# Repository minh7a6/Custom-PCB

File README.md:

# Custom-PCB
This is where I put my pcb and schematic that I created and used for projects.
PCB is created in Autodesk EAGLE.
For company to make those and get all the , I would recommend JLCPCB and LCSC for those since they are fast and quite cheap
You can use it and do whatever you want to do.
Feel free to put any request or issues. Because I'm still 17 so mistakes is unavoidable.
Enjoy :)

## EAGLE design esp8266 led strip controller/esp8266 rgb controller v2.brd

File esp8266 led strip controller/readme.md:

esp8266 wifi led strip controller

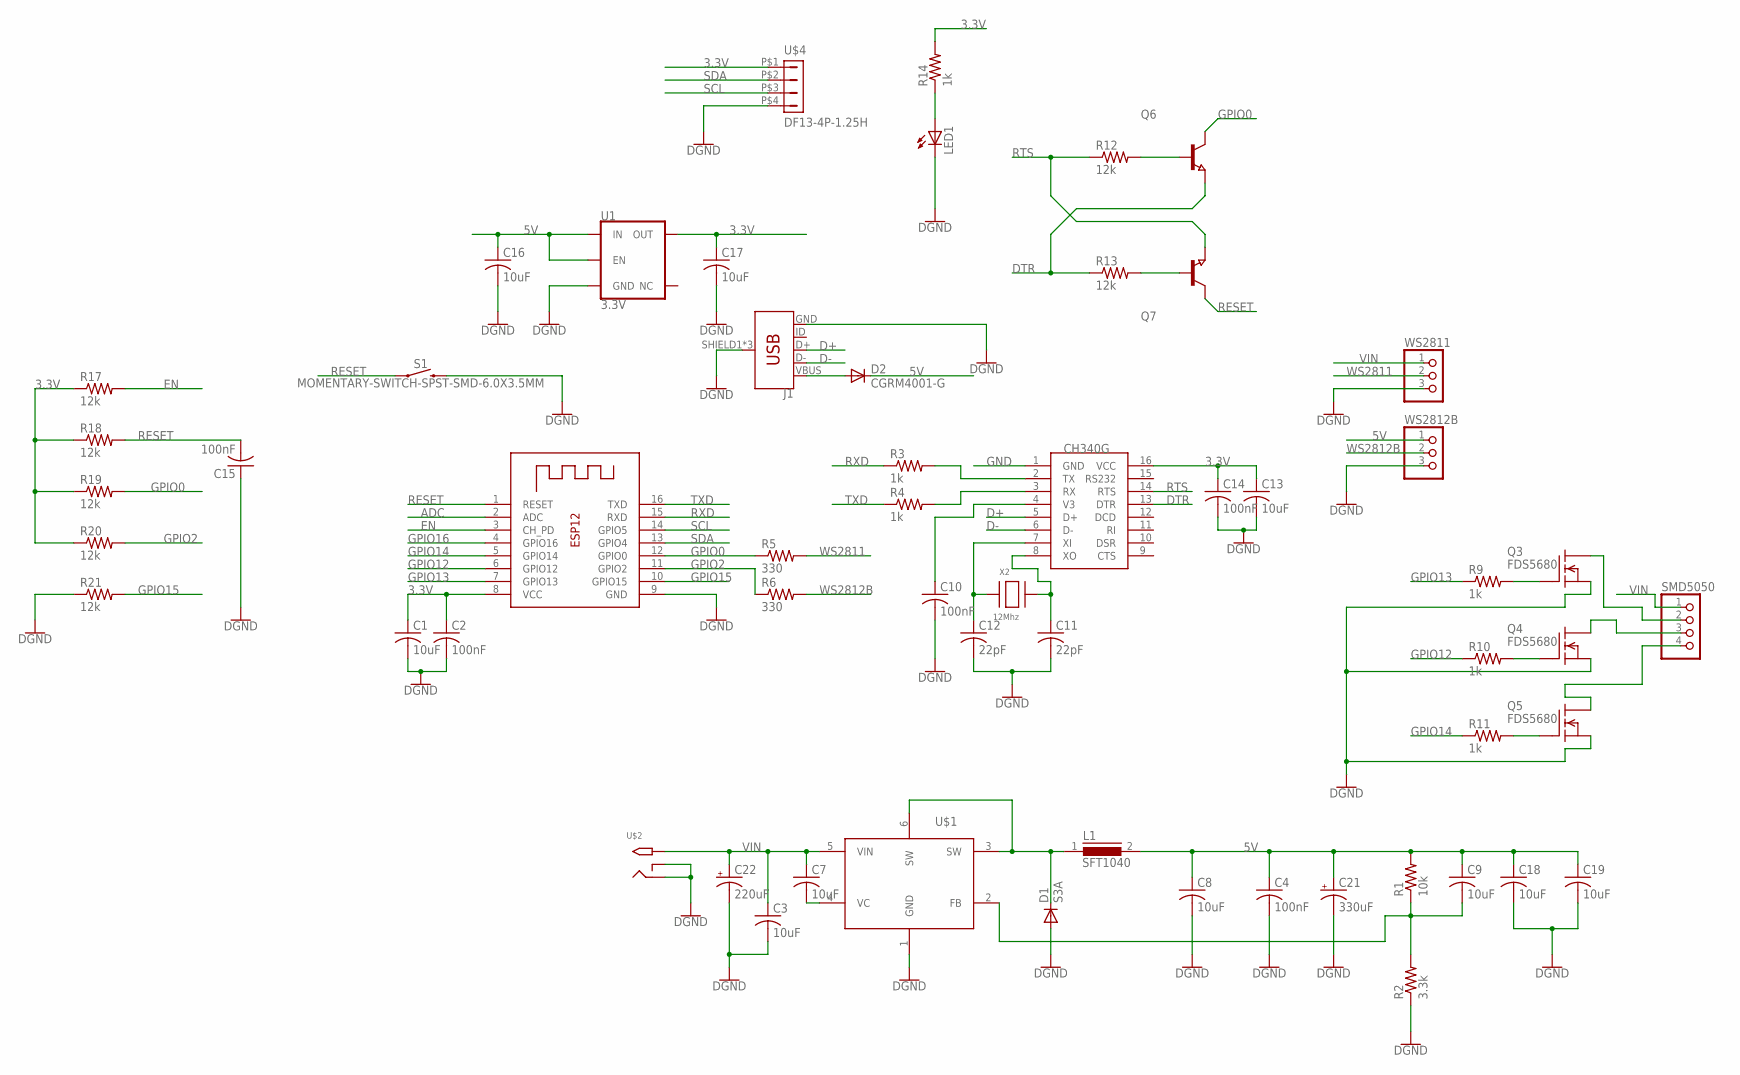
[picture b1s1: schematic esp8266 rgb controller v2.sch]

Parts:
C1, C3, C7, C8, C9, C13, C17, C18, C19: 10uF; C0805
C2, C4, C10, C14, C15: 100nF; C0805
C11, C12: 22pF; C0805
C16: 10uF; C1210
C21: 330uF; 153CLV-0810
C22: 220uF; 153CLV-0810
D1: S3A; DO214AB
D2: CGRM4001-G; SOD-123_MINI-SMA
J1: USB_MICRO-BREDUCED_PASTE; USB-B-MICRO-SMD_RED_PASTE
L1: SFT1040
LED1: LEDCHIP-LED0603; CHIP-LED0603
Q3, Q4, Q5: FDS5680; SO-8
Q6, Q7: NPN-TRANSISTOR_SOT23; SOT23
R1: 10k; R0805
R2: 3.3k; R0805
R3, R4, R9, R10, R11, R14: 1k; R0805
R5, R6: 330; R0805
R12, R13, R17, R18, R19, R20, R21: 12k; R0805
S1: MOMENTARY-SWITCH-SPST-SMD-6.0X3.5MM; TACTILE_SWITCH_SMD_6.0X3.5MM
SMD5050: PINHD-1X4; 1X04
U1: 3.3V; SOT23-5
U$1: XL4015; TO263-5
U$2: 2.1MMJACKTHM; PJ-102A
U$3: CH340G; SOIC16
U$4: DF13-4P-1.25H; DF13A-4P-1.25H
WS2811, WS2812B: PINHD-1X3; 1X03
X1: ESP-12F; ESP-12
X2: 12Mhz; NX5032

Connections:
3.3V: C1.1, C2.1, C13.1, C14.1, C17.1, R14.2, R17.1, R18.1, R19.1, R20.1, U1.5 (OUT), U$3.16 (VCC), U$4.P$1 (1), X1.8 (VCC)
5V: C4.1, C8.1, C9.1, C16.1, C18.1, C19.1, C21.+, D2.C, L1.2, R1.2, U1.1 (IN), U1.3 (EN), WS2812B.1
ADC: X1.2 (ADC)
D+: J1.D+, U$3.5 (D+)
D-: J1.D-, U$3.6 (D-)
DTR: Q6.2 (E), R13.1, U$3.13 (DTR)
EN: R17.2, X1.3 (CH_PD)
GND: C1.2, C2.2, C3.2, C4.2, C8.2, C10.2, C11.2, C12.2, C13.2, C14.2, C15.1, C16.2, C17.2, C18.2, C19.2, C21.-, C22.-, D1.A, J1.GND, J1.SHIELD1 (SHIELD), J1.SHIELD2 (SHIELD), J1.SHIELD3 (SHIELD), LED1.C, Q3.1 (S), Q3.2 (S), Q3.3 (S), Q4.1 (S), Q4.2 (S), Q4.3 (S), Q5.1 (S), Q5.2 (S), Q5.3 (S), R2.1, R21.1, S1.2, U1.2 (GND), U$1.1 (GND), U$2.RING, U$2.RING_SW, U$3.1 (GND), U$4.P$4 (4), WS2811.3, WS2812B.3, X1.9 (GND)
GPIO0: Q6.3 (C), R5.1, R19.2, X1.12 (GPIO0)
GPIO2: R6.1, R20.2, X1.11 (GPIO2)
GPIO12: R10.1, X1.6 (GPIO12)
GPIO13: R9.1, X1.7 (GPIO13)
GPIO14: R11.1, X1.5 (GPIO14)
GPIO15: R21.2, X1.10 (GPIO15)
GPIO16: X1.4 (GPIO16)
unnamed: Q3.5 (D), Q3.6 (D), Q3.7 (D), Q3.8 (D), SMD5050.2
unnamed: D1.C, L1.1, U$1.3 (SW), U$1.6 (SW)
unnamed: Q4.5 (D), Q4.6 (D), Q4.7 (D), Q4.8 (D), SMD5050.3
unnamed: D2.A, J1.VBUS
unnamed: R3.2, U$3.2 (TX)
unnamed: R4.2, U$3.3 (RX)
unnamed: C10.1, U$3.4 (V3)
unnamed: Q5.5 (D), Q5.6 (D), Q5.7 (D), Q5.8 (D), SMD5050.4
unnamed: Q6.1 (B), R12.2
unnamed: C12.1, U$3.7 (XI), X2.P$1
unnamed: C11.1, U$3.8 (XO), X2.P$2
unnamed: Q5.4 (G), R11.2
unnamed: Q7.1 (B), R13.2
unnamed: C7.2, U$1.4 (VC)
unnamed: Q4.4 (G), R10.2
unnamed: Q3.4 (G), R9.2
unnamed: LED1.A, R14.1
unnamed: C9.2, R1.1, R2.2, U$1.2 (FB)
RESET: C15.2, Q7.3 (C), R18.2, S1.1, X1.1 (RESET)
RTS: Q7.2 (E), R12.1, U$3.14 (RTS)
RXD: R3.1, X1.15 (RXD)
SCL: U$4.P$3 (3), X1.14 (GPIO5)
SDA: U$4.P$2 (2), X1.13 (GPIO4)
TXD: R4.1, X1.16 (TXD)
VIN: C3.1, C7.1, C22.+, SMD5050.1, U$1.5 (VIN), U$2.TIP, WS2811.1
WS2811: R5.2, WS2811.2
WS2812B: R6.2, WS2812B.2

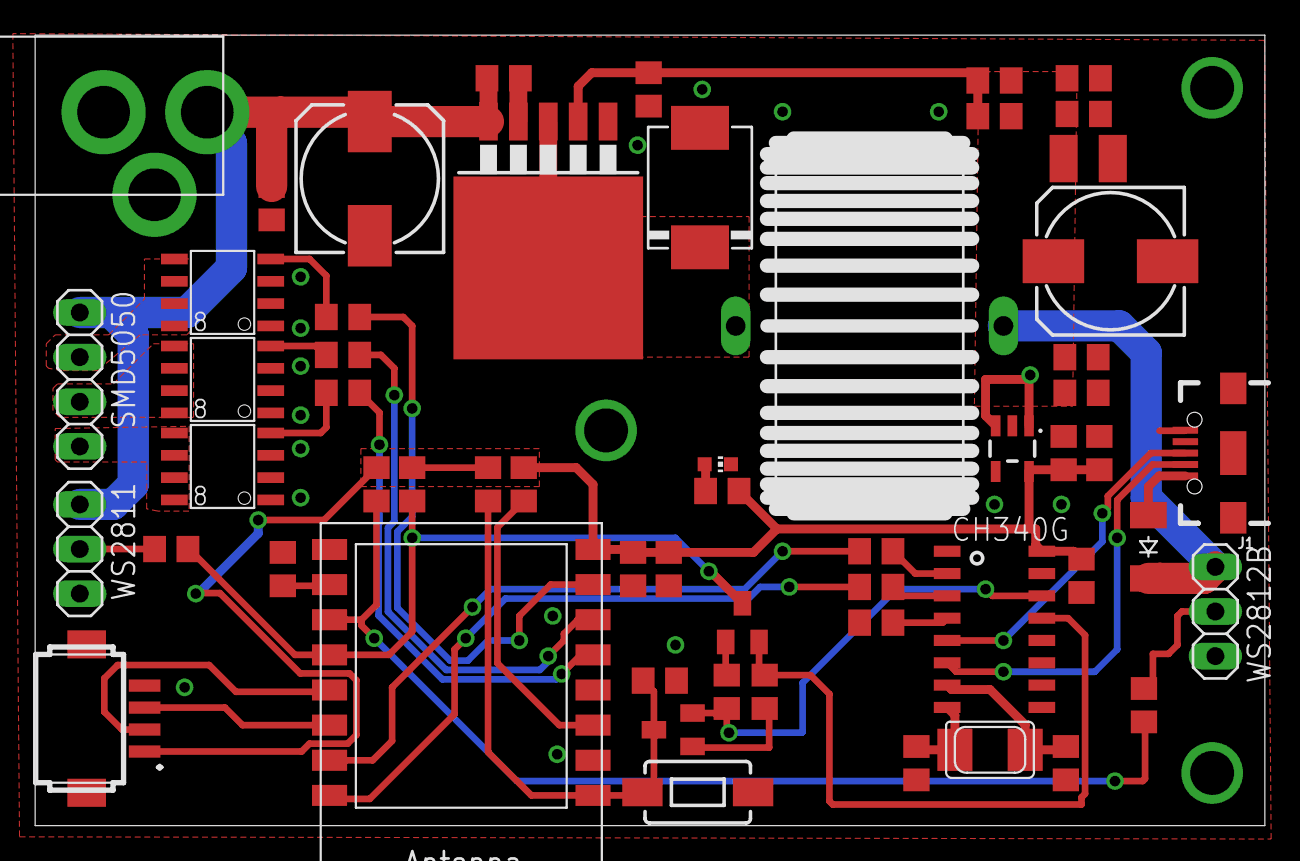
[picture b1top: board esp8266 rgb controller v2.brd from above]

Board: 2 copper layers, 70.0 x 45.0 mm, 57 parts (0 on the bottom side), 40 nets.

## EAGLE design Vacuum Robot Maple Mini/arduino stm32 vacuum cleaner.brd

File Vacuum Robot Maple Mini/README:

Vacuum Mainboard v1.0 + arduino ir reader

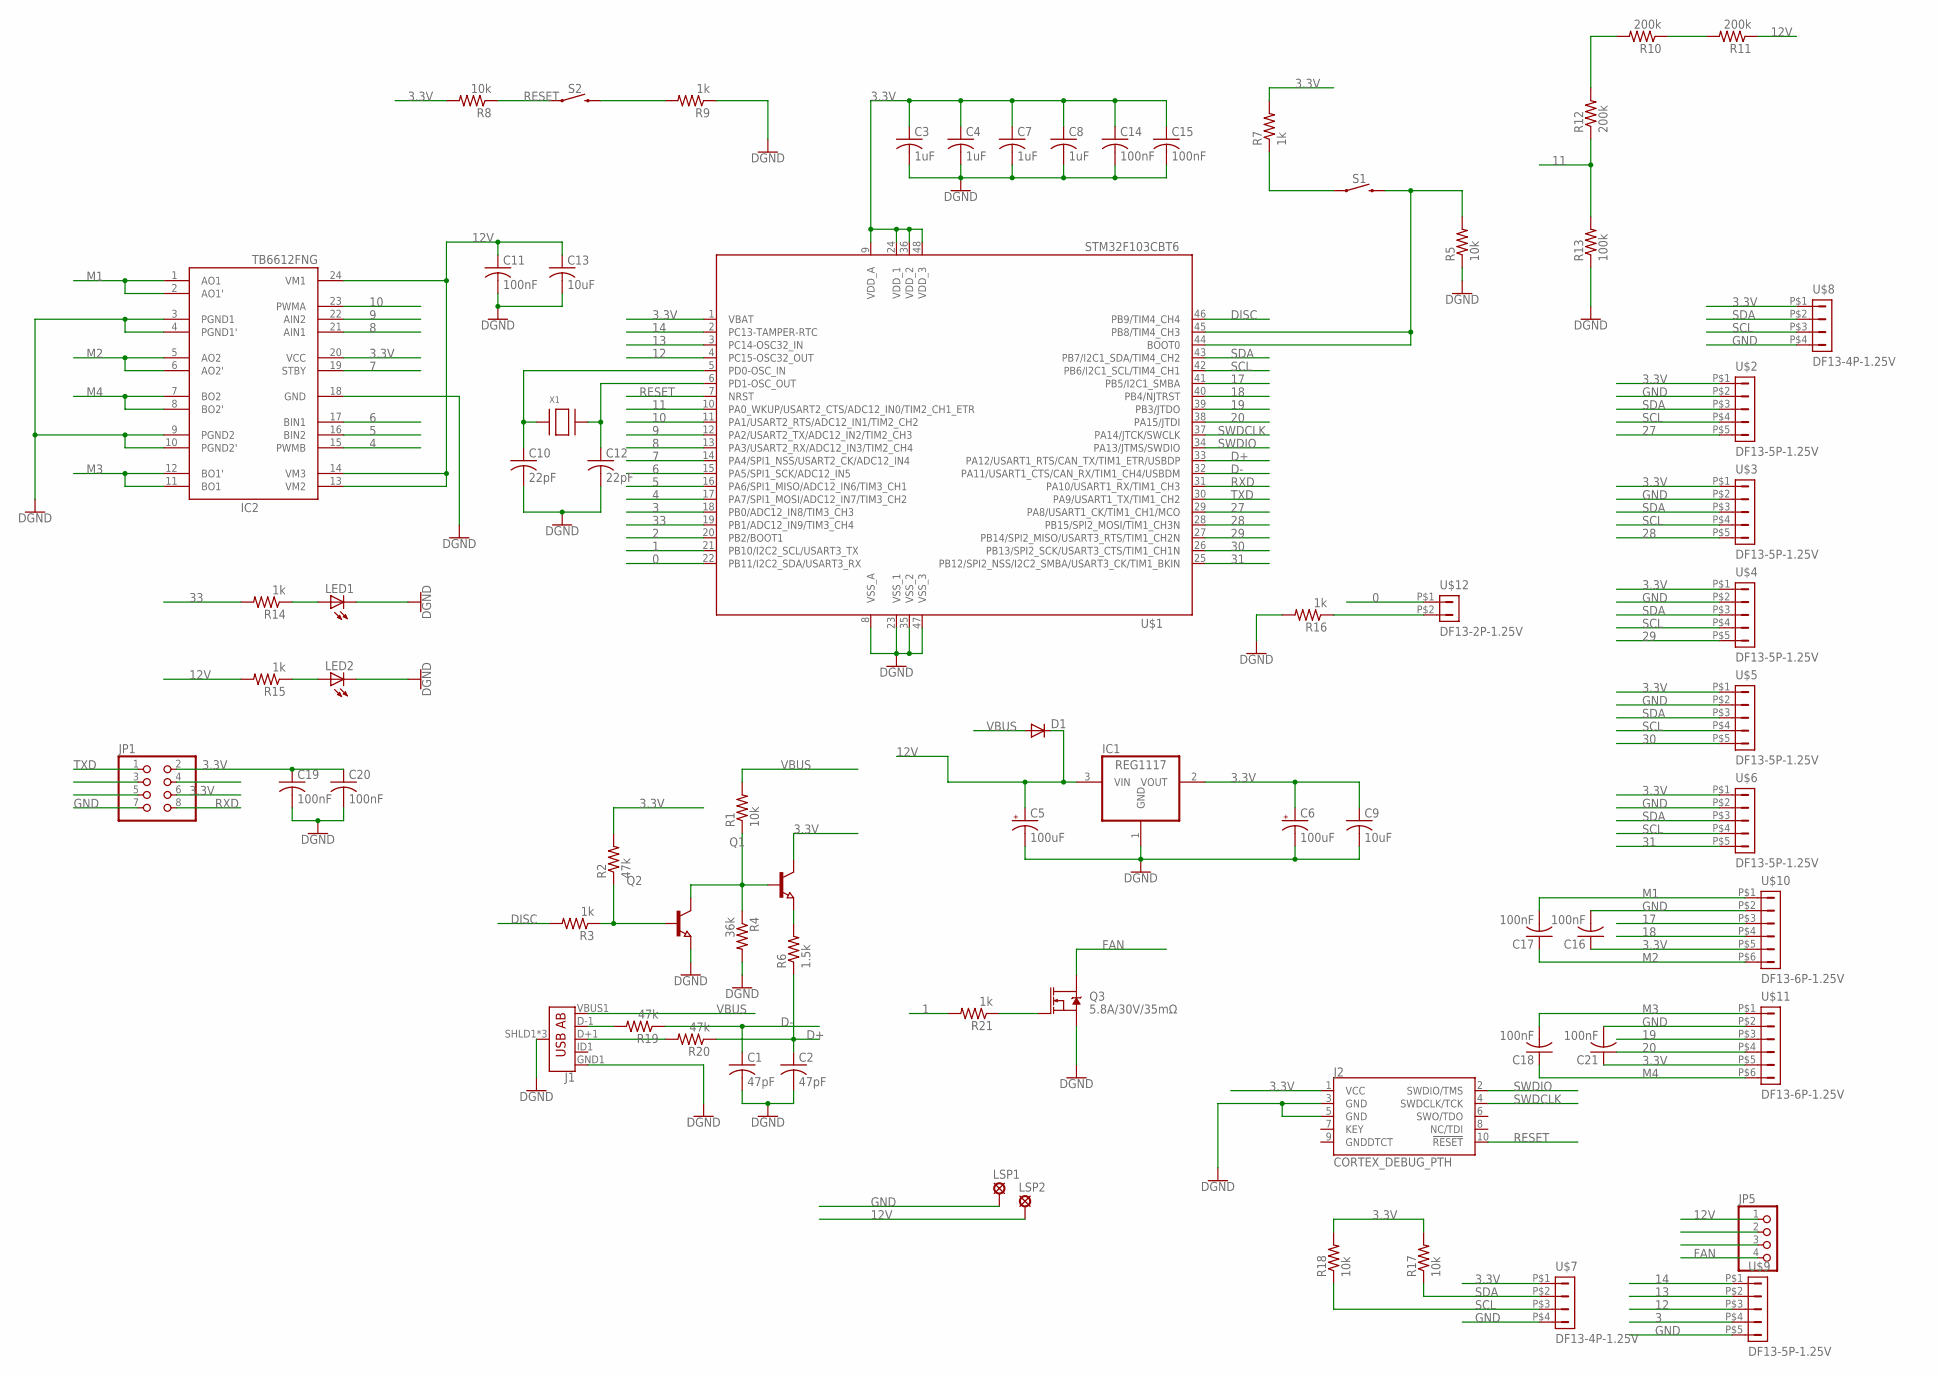
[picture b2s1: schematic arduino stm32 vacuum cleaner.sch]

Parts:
C1, C2: 47pF; C0805
C3, C4, C7, C8: 1uF; C0805
C5, C6: 100uF; CT7343
C9, C13: 10uF; C0805
C10, C12: 22pF; C0805
C11, C14, C15, C16, C17, C18, C19, C20, C21: 100nF; C0805
D1: DIODE-SOD123; SOD123
IC1: REG1117; SOT223
IC2: TB6612FNG; SSOP24
J1: USB_AB_SMT; USB-AB-MICRO-SMD
J2: CORTEX_DEBUG_PTH; 2X5-PTH-1.27MM
JP1: PINHD-2X4; 2X04
JP5: PINHD-1X4; 1X04
LED1, LED2: LEDCHIPLED_0603; CHIPLED_0603
LSP1, LSP2: SE14
Q1, Q2: NPN-TRANSISTOR_SOT23; SOT23
Q3: 5.8A/30V/35mΩ; SOT23-3
R1, R5, R8, R17, R18: 10k; R0805
R2, R19, R20: 47k; R0805
R3, R7, R9, R14, R15, R16, R21: 1k; R0805
R4: 36k; R0805
R6: 1.5k; R0805
R10, R11, R12: 200k; R1206
R13: 100k; R1206
S1, S2: MOMENTARY-SWITCH-SPST-SMD-6.0X3.5MM; TACTILE_SWITCH_SMD_6.0X3.5MM
U$1: STM32F103CBT6; STM32_LQFP48
U$2, U$3, U$4, U$5, U$6, U$9: DF13-5P-1.25V; DF13C-5P-1.25V
U$7, U$8: DF13-4P-1.25V; DF13C-4P-1.25V
U$10, U$11: DF13-6P-1.25V; DF13C-6P-1.25V
U$12: DF13-2P-1.25V; DF13C-2P-1.25V
X1: XTALNX5032; NX5032

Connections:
0: U$1.22 (PB11/I2C2_SDA/USART3_RX), U$12.P$1 (1)
1: R21.2, U$1.21 (PB10/I2C2_SCL/USART3_TX)
2: U$1.20 (PB2/BOOT1)
3: U$1.18 (PB0/ADC12_IN8/TIM3_CH3), U$9.P$4 (4)
3.3V: C3.1, C4.1, C6.+, C7.1, C8.1, C9.1, C14.1, C15.1, C16.1, C19.1, C20.1, C21.1, IC1.2 (VOUT), IC2.20 (VCC), J2.1 (VCC), JP1.2, JP1.6, Q1.3 (C), R2.2, R7.2, R8.2, R17.2, R18.2, U$1.1 (VBAT), U$1.9 (VDD_A), U$1.24 (VDD_1), U$1.36 (VDD_2), U$1.48 (VDD_3), U$2.P$1 (1), U$3.P$1 (1), U$4.P$1 (1), U$5.P$1 (1), U$6.P$1 (1), U$7.P$1 (1), U$8.P$1 (1), U$10.P$5 (5), U$11.P$5 (5)
4: IC2.15 (PWMB), U$1.17 (PA7/SPI1_MOSI/ADC12_IN7/TIM3_CH2)
5: IC2.16 (BIN2), U$1.16 (PA6/SPI1_MISO/ADC12_IN6/TIM3_CH1)
6: IC2.17 (BIN1), U$1.15 (PA5/SPI1_SCK/ADC12_IN5)
7: IC2.19 (STBY), U$1.14 (PA4/SPI1_NSS/USART2_CK/ADC12_IN4)
8: IC2.21 (AIN1), U$1.13 (PA3/USART2_RX/ADC12_IN3/TIM2_CH4)
9: IC2.22 (AIN2), U$1.12 (PA2/USART2_TX/ADC12_IN2/TIM2_CH3)
10: IC2.23 (PWMA), U$1.11 (PA1/USART2_RTS/ADC12_IN1/TIM2_CH2)
11: R12.1, R13.2, U$1.10 (PA0_WKUP/USART2_CTS/ADC12_IN0/TIM2_CH1_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)
12: U$1.4 (PC15-OSC32_OUT), U$9.P$3 (3)
12V: C5.+, C11.1, C13.1, D1.C, IC1.3 (VIN), IC2.13 (VM2), IC2.14 (VM3), IC2.24 (VM1), JP5.1, LSP2.MP, R11.1, R15.2
13: U$1.3 (PC14-OSC32_IN), U$9.P$2 (2)
14: U$1.2 (PC13-TAMPER-RTC), U$9.P$1 (1)
17: U$1.41 (PB5/I2C1_SMBA), U$10.P$3 (3)
18: U$1.40 (PB4/NJTRST), U$10.P$4 (4)
19: U$1.39 (PB3/JTDO), U$11.P$3 (3)
20: U$1.38 (PA15/JTDI), U$11.P$4 (4)
27: U$1.29 (PA8/USART1_CK/TIM1_CH1/MCO), U$2.P$5 (5)
28: U$1.28 (PB15/SPI2_MOSI/TIM1_CH3N), U$3.P$5 (5)
29: U$1.27 (PB14/SPI2_MISO/USART3_RTS/TIM1_CH2N), U$4.P$5 (5)
30: U$1.26 (PB13/SPI2_SCK/USART3_CTS/TIM1_CH1N), U$5.P$5 (5)
31: U$1.25 (PB12/SPI2_NSS/I2C2_SMBA/USART3_CK/TIM1_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), U$6.P$5 (5)
33: R14.2, U$1.19 (PB1/ADC12_IN9/TIM3_CH4)
D+: C2.1, R6.1, R20.1, U$1.33 (PA12/USART1_RTS/CAN_TX/TIM1_ETR/USBDP)
D-: C1.1, R19.1, U$1.32 (PA11/USART1_CTS/CAN_RX/TIM1_CH4/USBDM)
DISC: R3.2, U$1.46 (PB9/TIM4_CH4)
FAN: JP5.4, Q3.3 (D)
GND: C1.2, C2.2, C3.2, C4.2, C5.-, C6.-, C7.2, C8.2, C9.2, C10.2, C11.2, C12.2, C13.2, C14.2, C15.2, C16.2, C19.2, C20.2, C21.2, IC1.1 (GND), IC2.3 (PGND1), IC2.4 (PGND1'), IC2.9 (PGND2), IC2.10 (PGND2'), IC2.18 (GND), J1.GND1 (GND), J1.SHLD1 (SHIELD), J1.SHLD2 (SHIELD), J1.SHLD3 (SHIELD), J2.3 (GND), J2.5 (GND), JP1.7, LED1.C, LED2.C, LSP1.MP, Q2.2 (E), Q3.2 (S), R4.2, R5.1, R9.1, R13.1, R16.2, U$1.8 (VSS_A), U$1.23 (VSS_1), U$1.35 (VSS_2), U$1.47 (VSS_3), U$2.P$2 (2), U$3.P$2 (2), U$4.P$2 (2), U$5.P$2 (2), U$6.P$2 (2), U$7.P$4 (4), U$8.P$4 (4), U$9.P$5 (5), U$10.P$2 (2), U$11.P$2 (2)
M1: C17.2, IC2.1 (AO1), IC2.2 (AO1'), U$10.P$1 (1)
M2: C17.1, IC2.5 (AO2), IC2.6 (AO2'), U$10.P$6 (6)
M3: C18.2, IC2.11 (BO1), IC2.12 (BO1'), U$11.P$1 (1)
M4: C18.1, IC2.7 (BO2), IC2.8 (BO2'), U$11.P$6 (6)
unnamed: J1.D-1 (D-), R19.2
unnamed: J1.D+1 (D+), R20.2
unnamed: R5.2, S1.2, U$1.44 (BOOT0), U$1.45 (PB8/TIM4_CH3)
unnamed: Q1.2 (E), R6.2
unnamed: Q1.1 (B), Q2.3 (C), R1.1, R4.1
unnamed: C10.1, U$1.5 (PD0-OSC_IN), X1.P$1
unnamed: R7.1, S1.1
unnamed: Q2.1 (B), R2.1, R3.1
unnamed: R16.1, U$12.P$2 (2)
unnamed: R10.2, R12.2
unnamed: Q3.1 (G), R21.1
unnamed: LED1.A, R14.1
unnamed: LED2.A, R15.1
unnamed: R10.1, R11.2
unnamed: R9.2, S2.2
unnamed: C12.1, U$1.6 (PD1-OSC_OUT), X1.P$2
RESET: J2.10 (!RESET), R8.1, S2.1, U$1.7 (NRST)
RXD: JP1.8, U$1.31 (PA10/USART1_RX/TIM1_CH3)
SCL: R18.1, U$1.42 (PB6/I2C1_SCL/TIM4_CH1), U$2.P$4 (4), U$3.P$4 (4), U$4.P$4 (4), U$5.P$4 (4), U$6.P$4 (4), U$7.P$3 (3), U$8.P$3 (3)
SDA: R17.1, U$1.43 (PB7/I2C1_SDA/TIM4_CH2), U$2.P$3 (3), U$3.P$3 (3), U$4.P$3 (3), U$5.P$3 (3), U$6.P$3 (3), U$7.P$2 (2), U$8.P$2 (2)
SWDCLK: J2.4 (SWDCLK/TCK), U$1.37 (PA14/JTCK/SWCLK)
SWDIO: J2.2 (SWDIO/TMS), U$1.34 (PA13/JTMS/SWDIO)
TXD: JP1.1, U$1.30 (PA9/USART1_TX/TIM1_CH2)
VBUS: D1.A, J1.VBUS1 (VBUS), R1.2

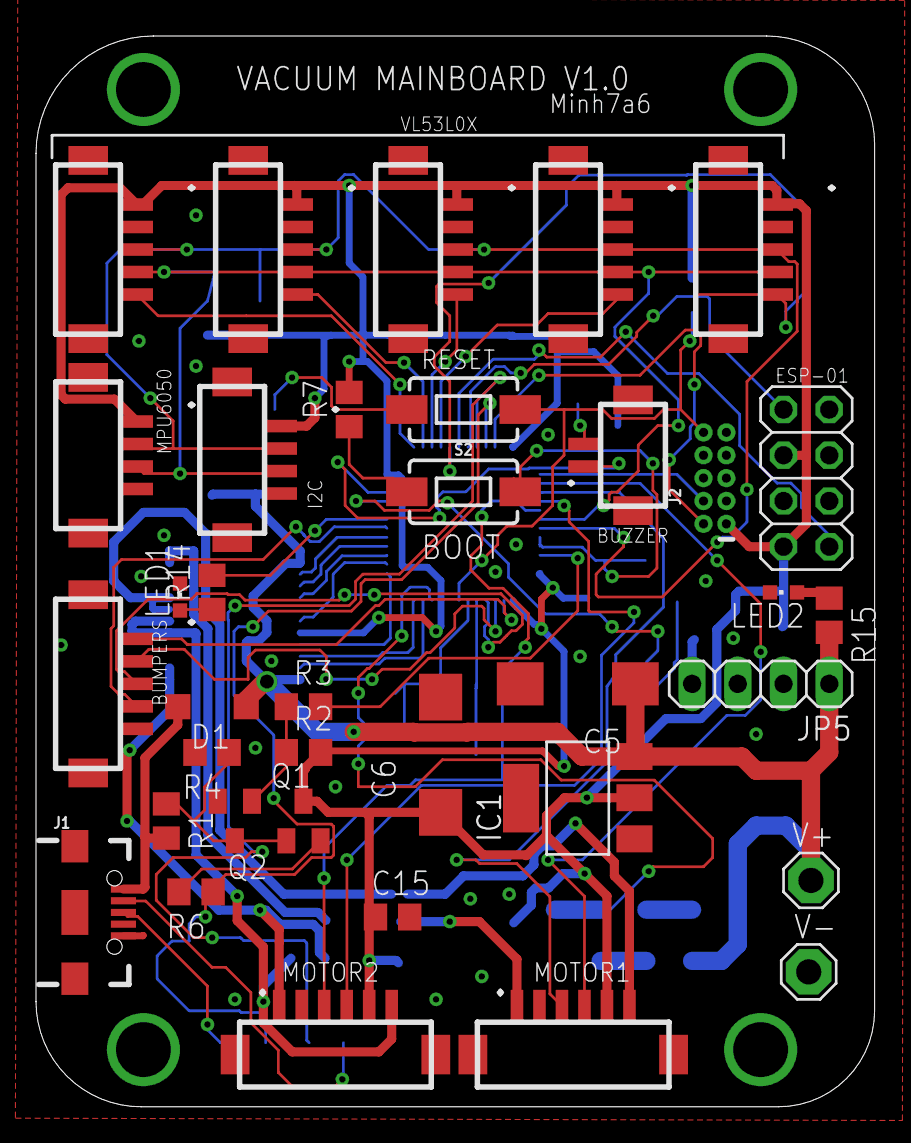
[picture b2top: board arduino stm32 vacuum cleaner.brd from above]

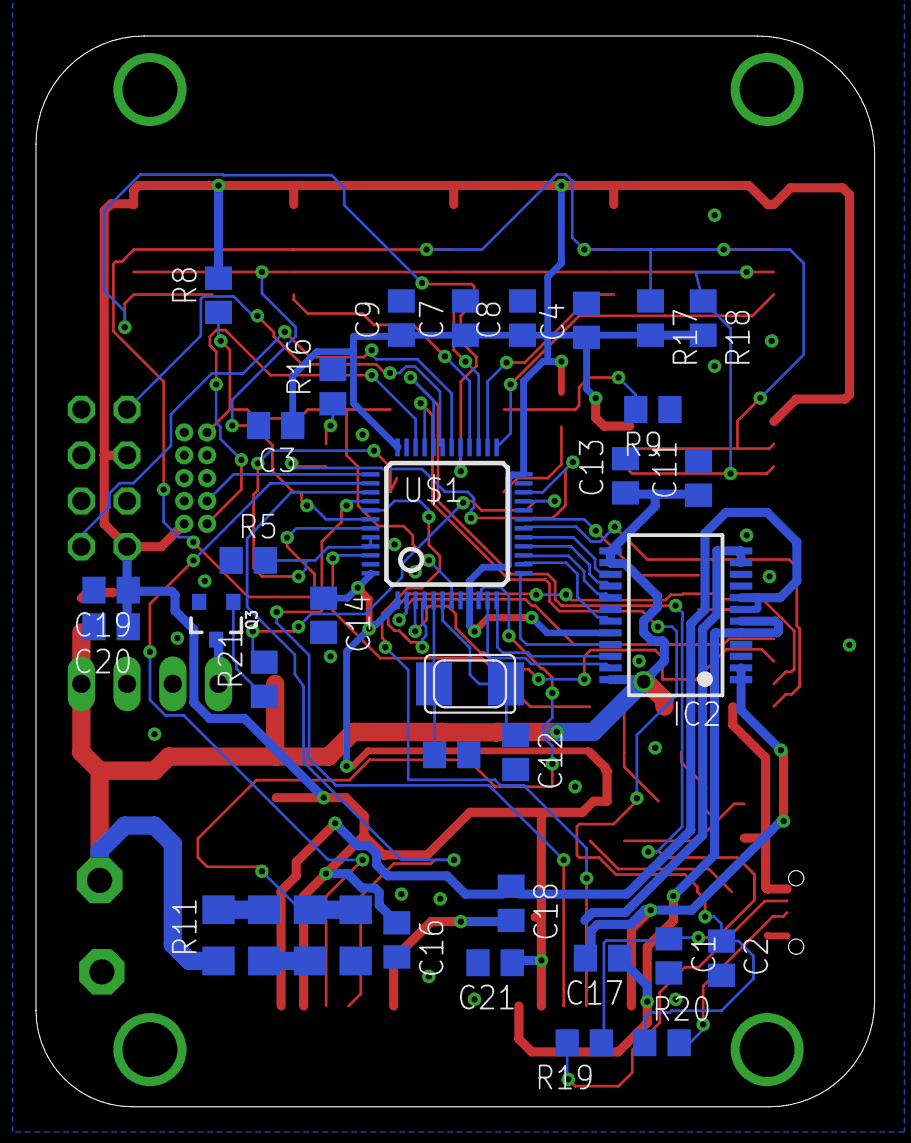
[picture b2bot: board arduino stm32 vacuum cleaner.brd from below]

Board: 2 copper layers, 46.6 x 59.5 mm, 71 parts (35 on the bottom side), 59 nets.

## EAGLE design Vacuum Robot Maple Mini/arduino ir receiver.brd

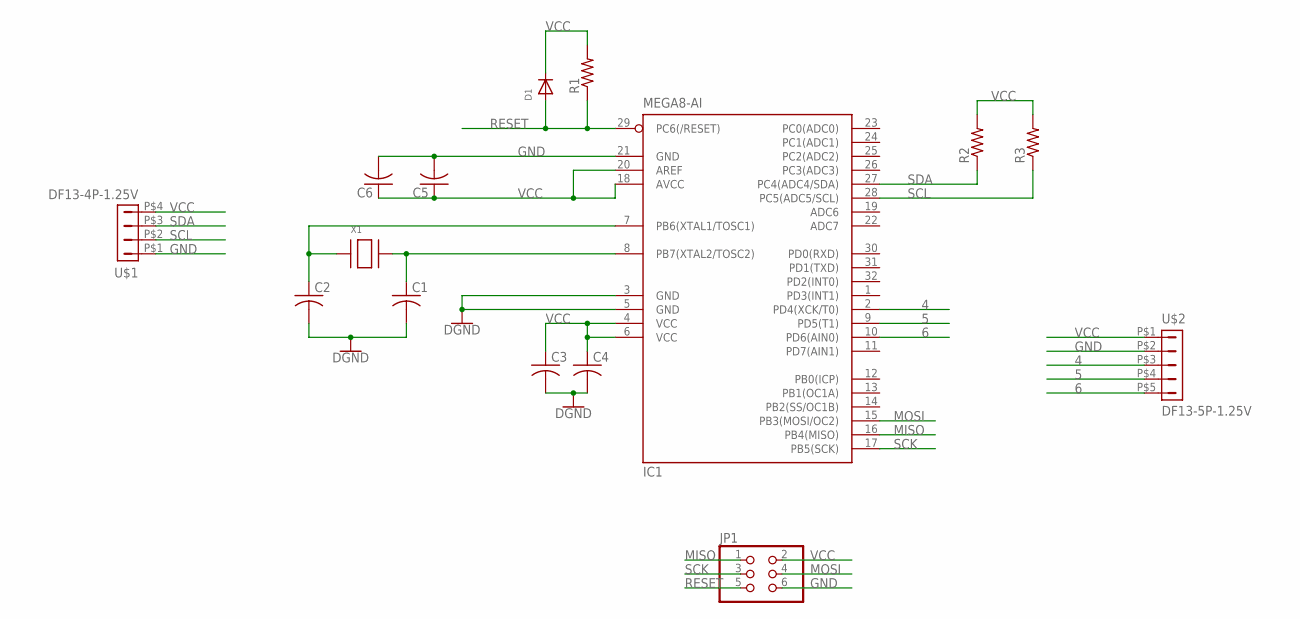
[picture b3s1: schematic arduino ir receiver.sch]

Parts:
C1, C2, C3, C4, C5, C6: C-USC0805; C0805
D1: DIODESOD-123; SOD-123
IC1: MEGA8-AI; TQFP32-08
JP1: PINHD-2X3; 2X03
R1, R2, R3: R-US_R0805; R0805
U$1: DF13-4P-1.25V; DF13C-4P-1.25V
U$2: DF13-5P-1.25V; DF13C-5P-1.25V
X1: XTALNX5032; NX5032

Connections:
4: IC1.2 (PD4(XCK/T0)), U$2.P$3 (3)
5: IC1.9 (PD5(T1)), U$2.P$4 (4)
6: IC1.10 (PD6(AIN0)), U$2.P$5 (5)
GND: C1.2, C2.2, C3.2, C4.2, C5.2, C6.2, IC1.3 (GND), IC1.5 (GND), IC1.21 (GND), JP1.6, U$1.P$1 (1), U$2.P$2 (2)
MISO: IC1.16 (PB4(MISO)), JP1.1
MOSI: IC1.15 (PB3(MOSI/OC2)), JP1.4
unnamed: C1.1, IC1.8 (PB7(XTAL2/TOSC2)), X1.P$2
unnamed: C2.1, IC1.7 (PB6(XTAL1/TOSC1)), X1.P$1
RESET: D1.A, IC1.29 (PC6(/RESET)), JP1.5, R1.1
SCK: IC1.17 (PB5(SCK)), JP1.3
SCL: IC1.28 (PC5(ADC5/SCL)), R3.1, U$1.P$2 (2)
SDA: IC1.27 (PC4(ADC4/SDA)), R2.1, U$1.P$3 (3)
VCC: C3.1, C4.1, C5.1, C6.1, D1.C, IC1.4 (VCC), IC1.6 (VCC), IC1.18 (AVCC), IC1.20 (AREF), JP1.2, R1.2, R2.2, R3.2, U$1.P$4 (4), U$2.P$1 (1)

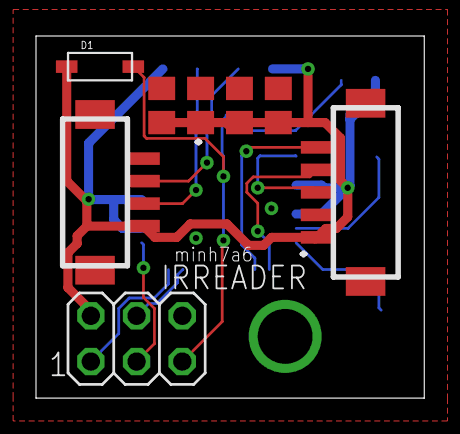
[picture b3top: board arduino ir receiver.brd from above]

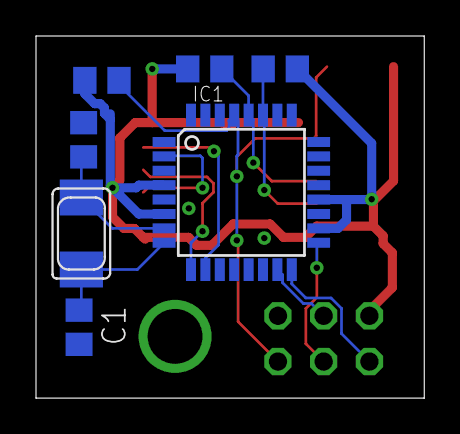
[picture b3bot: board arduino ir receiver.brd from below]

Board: 2 copper layers, 21.6 x 20.1 mm, 15 parts (7 on the bottom side), 13 nets.

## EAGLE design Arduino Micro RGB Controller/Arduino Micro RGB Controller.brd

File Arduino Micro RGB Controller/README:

Arduino Micro RGB Controller
Supported WS2811; Normal 3258, 5050 LED Strip

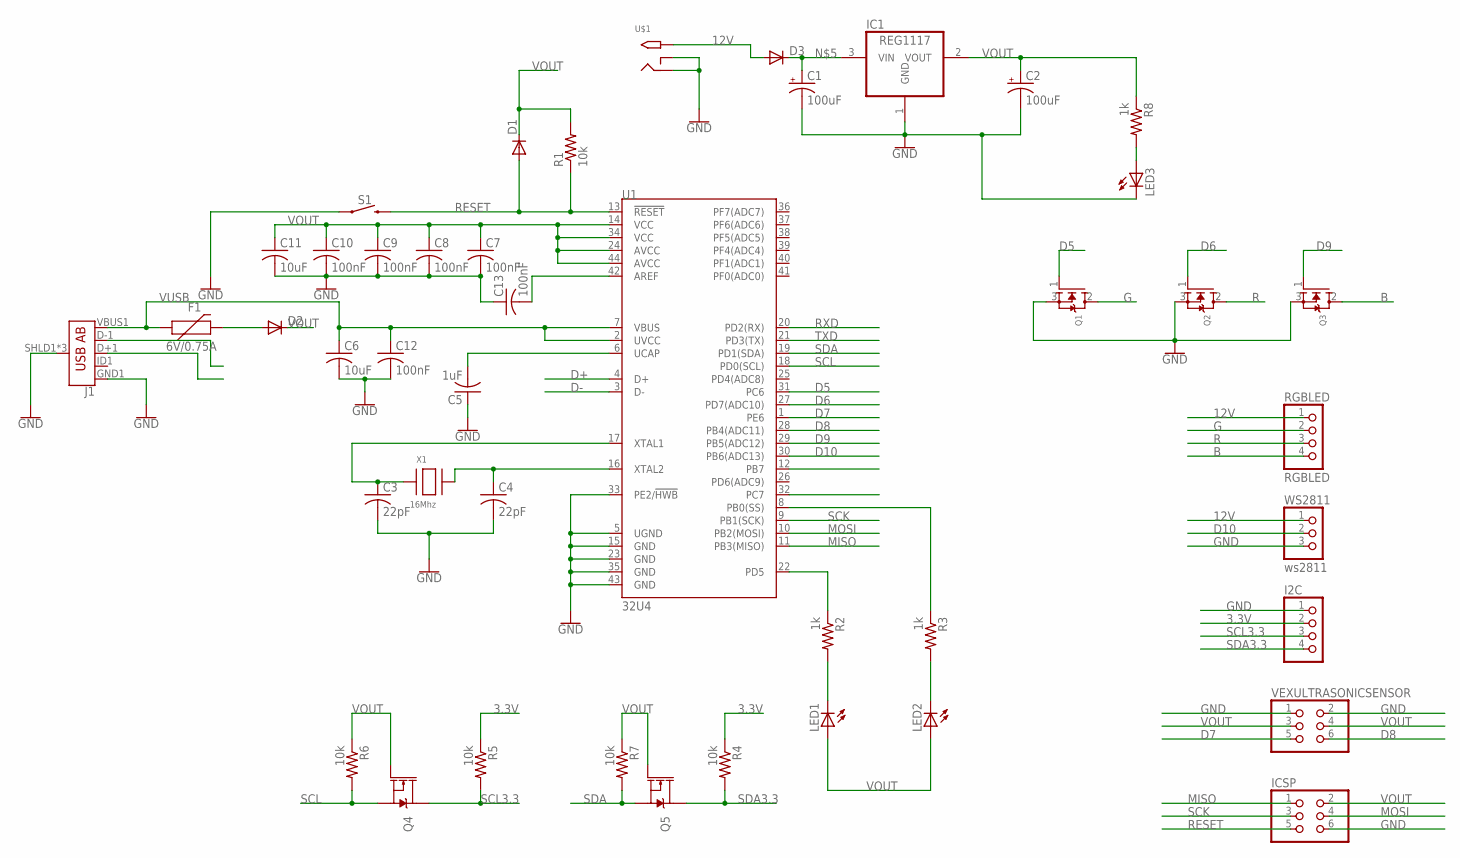
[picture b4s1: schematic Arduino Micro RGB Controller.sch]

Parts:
C1, C2: 100uF; CT7343
C3, C4: 22pF; C0805
C5: 1uF; C0805
C6, C11: 10uF; C0805
C7, C8, C9, C10, C12, C13: 100nF; C0805
D1, D2, D3: DIODE-SOD123; SOD123
F1: 6V/0.75A; 1206
I2C: PINHD-1X4; 1X04
IC1: REG1117; SOT223
ICSP: PINHD-2X3; 2X03
J1: USB_AB_SMT; USB-AB-MICRO-SMD
LED1, LED2, LED3: LEDCHIPLED_0603; CHIPLED_0603
Q1, Q2, Q3: MOSFET-NGDS_TO220V; TO220V
Q4, Q5: 220mA/50V/3.5Ω; SOT23-3
R1, R4, R5, R6, R7: 10k; M0805
R2, R3, R8: 1k; M0805
RGBLED: RGBLED; 1X04
S1: MOMENTARY-SWITCH-SPST-SMD-6.0X3.5MM; TACTILE_SWITCH_SMD_6.0X3.5MM
U1: 32U4; TQFP44
U$1: 2.1MMJACKTHM; PJ-102A
VEXULTRASONICSENSOR: PINHD-2X3; 2X03
WS2811: ws2811; 1X03
X1: 16Mhz; NX5032

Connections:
3.3V: I2C.2, R4.1, R5.1
12V: D3.A, RGBLED.1, U$1.TIP, WS2811.1
B: Q3.2 (D), RGBLED.4
D5: Q1.1 (G), U1.31 (PC6)
D6: Q2.1 (G), U1.27 (PD7(ADC10))
D7: U1.1 (PE6), VEXULTRASONICSENSOR.5
D8: U1.28 (PB4(ADC11)), VEXULTRASONICSENSOR.6
D9: Q3.1 (G), U1.29 (PB5(ADC12))
D10: U1.30 (PB6(ADC13)), WS2811.2
D+: J1.D+1 (D+), U1.4 (D+)
D-: J1.D-1 (D-), U1.3 (D-)
G: Q1.2 (D), RGBLED.2
GND: C1.-, C2.-, C3.2, C4.2, C5.1, C6.2, C7.2, C8.2, C9.2, C10.2, C11.2, C12.2, C13.1, I2C.1, IC1.1 (GND), ICSP.6, J1.GND1 (GND), J1.SHLD1 (SHIELD), J1.SHLD2 (SHIELD), J1.SHLD3 (SHIELD), LED3.C, Q1.3 (S), Q2.3 (S), Q3.3 (S), S1.1, U1.5 (UGND), U1.15 (GND), U1.23 (GND), U1.33 (PE2/!HWB), U1.35 (GND), U1.43 (GND), U$1.RING, U$1.RING_SW, VEXULTRASONICSENSOR.1, VEXULTRASONICSENSOR.2, WS2811.3
MISO: ICSP.1, U1.11 (PB3(MISO))
MOSI: ICSP.4, U1.10 (PB2(MOSI))
unnamed: LED1.C, R2.2
unnamed: LED3.A, R8.2
unnamed: R3.1, U1.8 (PB0(SS))
unnamed: C5.2, U1.6 (UCAP)
unnamed: C1.+, D3.C, IC1.3 (VIN)
unnamed: LED2.C, R3.2
unnamed: C3.1, U1.17 (XTAL1), X1.P$1
unnamed: C4.1, U1.16 (XTAL2), X1.P$2
unnamed: C13.2, U1.42 (AREF)
unnamed: R2.1, U1.22 (PD5)
unnamed: D2.A, F1.2
R: Q2.2 (D), RGBLED.3
RESET: D1.A, ICSP.5, R1.1, S1.2, U1.13 (!RESET)
RXD: U1.20 (PD2(RX))
SCK: ICSP.3, U1.9 (PB1(SCK))
SCL: Q4.2 (S), R6.2, U1.18 (PD0(SCL))
SCL3.3: I2C.3, Q4.3 (D), R5.2
SDA: Q5.2 (S), R7.2, U1.19 (PD1(SDA))
SDA3.3: I2C.4, Q5.3 (D), R4.2
TXD: U1.21 (PD3(TX))
VOUT: C2.+, C7.1, C8.1, C9.1, C10.1, C11.1, D1.C, D2.C, IC1.2 (VOUT), ICSP.2, LED1.A, LED2.A, Q4.1 (G), Q5.1 (G), R1.2, R6.1, R7.1, R8.1, U1.14 (VCC), U1.24 (AVCC), U1.34 (VCC), U1.44 (AVCC), VEXULTRASONICSENSOR.3, VEXULTRASONICSENSOR.4
VUSB: C6.1, C12.1, F1.1, J1.VBUS1 (VBUS), U1.2 (UVCC), U1.7 (VBUS)

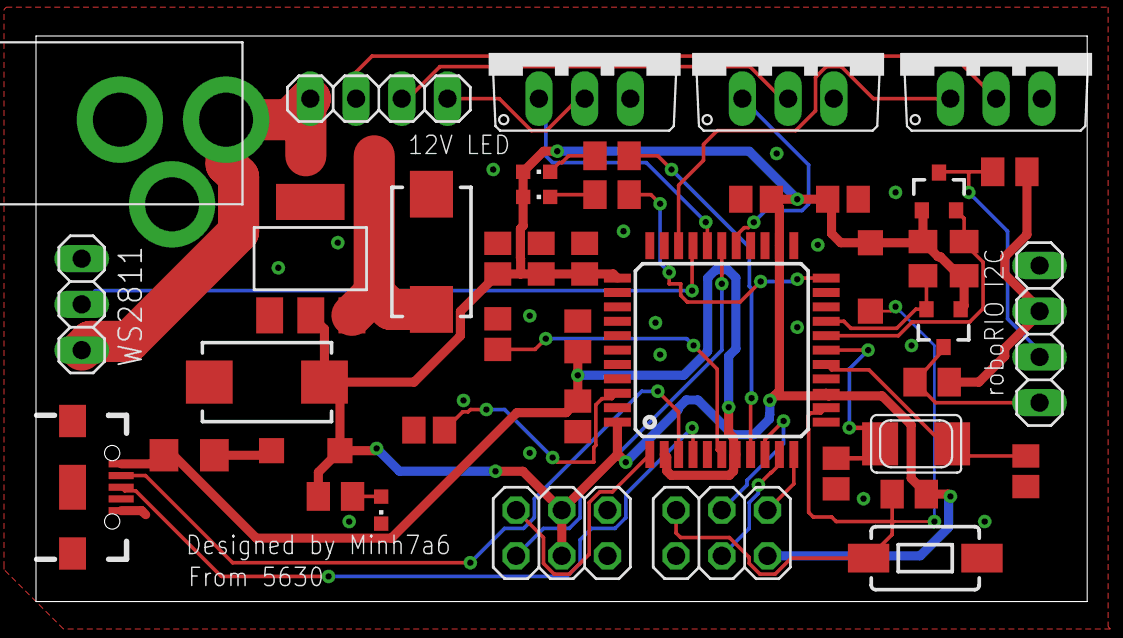
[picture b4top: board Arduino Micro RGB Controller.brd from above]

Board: 2 copper layers, 58.4 x 31.4 mm, 44 parts (0 on the bottom side), 35 nets.

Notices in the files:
parts and their libraries:
SparkFun-Fuses: Licensing: Creative Commons ShareAlike 4.0 International - https://creativecommons.org/licenses/by-sa/4.0
